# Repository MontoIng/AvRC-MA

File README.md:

# AvRC-MA
Avión RC - Monitoreo Ambiental
- En este proyecto se realizó un avión RC (Radio - Control) capaz de tomar datos de temperatura, presión y humedad.
(Santiago Montoya M.)
- Se subió cada codificación usada y creada en la realización del proyecto.
  Siendo asi estos: - Código del control.
                    - Código del Avión.
                    - Código para calibrar el motor.
                    - Librería BME280.
- Se organizó por carpeta los códigos, diseños (muestras - evidencias), documentos y PCBs.
- Se subieron los documentos respectivos a las carpetas.

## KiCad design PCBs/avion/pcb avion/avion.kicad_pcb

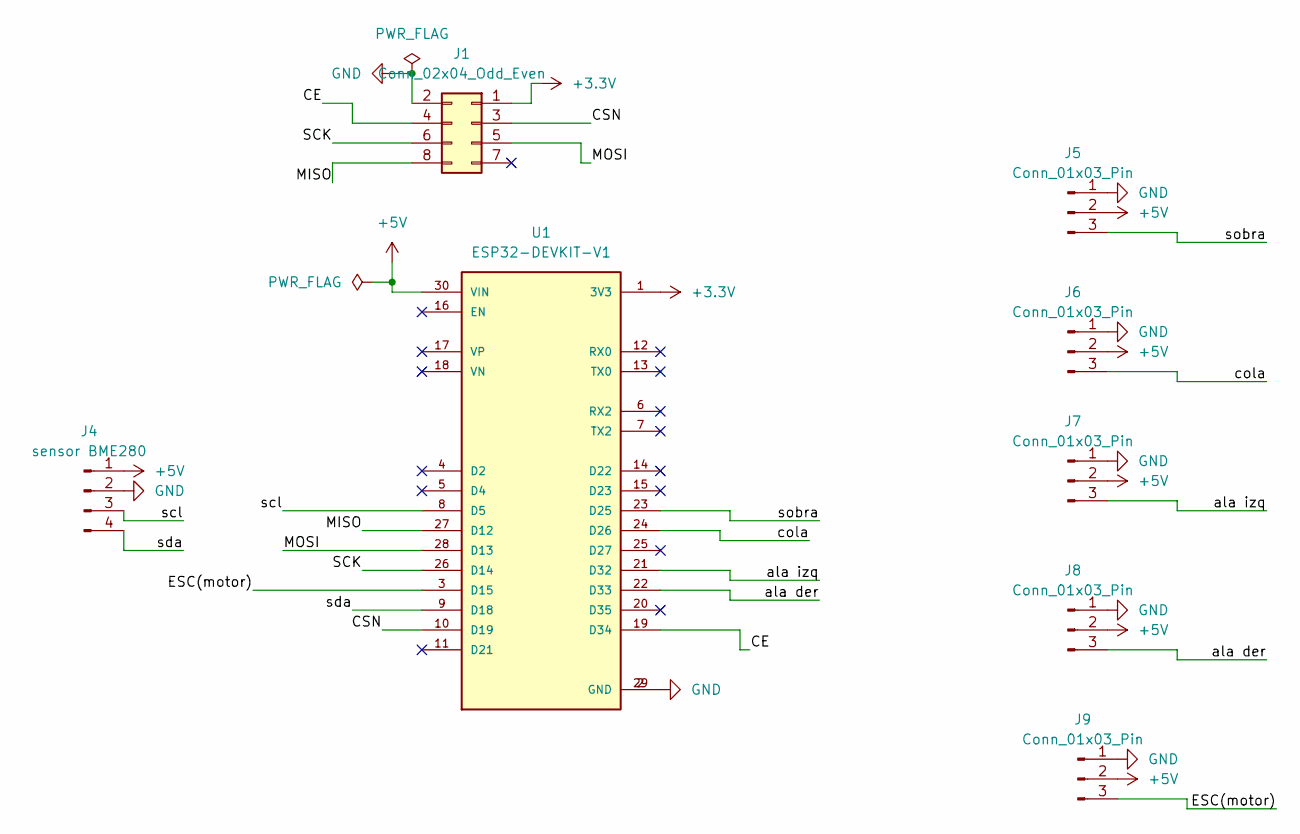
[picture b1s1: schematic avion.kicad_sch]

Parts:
J1: Conn_02x04_Odd_Even; PinSocket_2x04_P2.54mm_Vertical
J4: sensor BME280; PinHeader_1x04_P2.54mm_Vertical
J5, J6, J7, J8, J9: Conn_01x03_Pin; PinHeader_1x03_P2.54mm_Vertical
U1: ESP32-DEVKIT-V1; MODULE_ESP32_DEVKIT_V1; PARTREV N/A

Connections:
+3.3V: J1.1, U1.1 (3V3)
+5V: J4.1, J5.2, J6.2, J7.2, J8.2, J9.2, U1.30 (VIN)
/CE: J1.4, U1.19 (D34)
/CSN: J1.3, U1.10 (D19)
/ESC(motor): J9.3, U1.3 (D15)
/MISO: J1.8, U1.27 (D12)
/MOSI: J1.5, U1.28 (D13)
/SCK: J1.6, U1.26 (D14)
/ala der: J8.3, U1.22 (D33)
/ala izq: J7.3, U1.21 (D32)
/cola: J6.3, U1.24 (D26)
/scl: J4.3, U1.8 (D5)
/sda: J4.4, U1.9 (D18)
/sobra: J5.3, U1.23 (D25)
GND: J1.2, J4.2, J5.1, J6.1, J7.1, J8.1, J9.1, U1.2 (GND), U1.29 (GND)

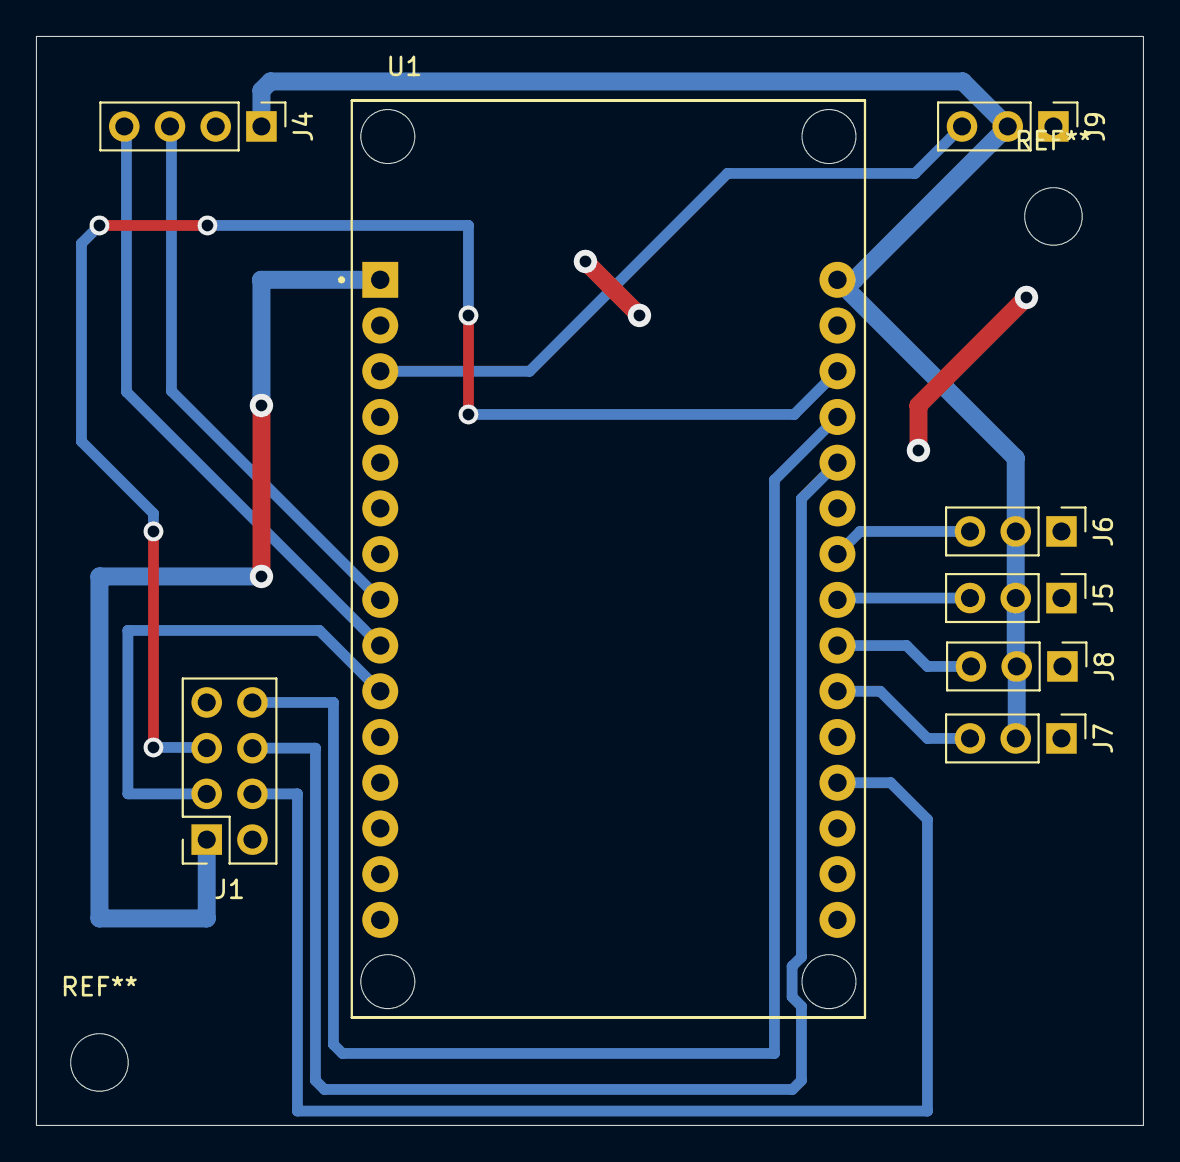
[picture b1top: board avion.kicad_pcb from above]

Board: 2 copper layers, 61.5 x 60.5 mm, 8 parts (0 on the bottom side), 15 nets.

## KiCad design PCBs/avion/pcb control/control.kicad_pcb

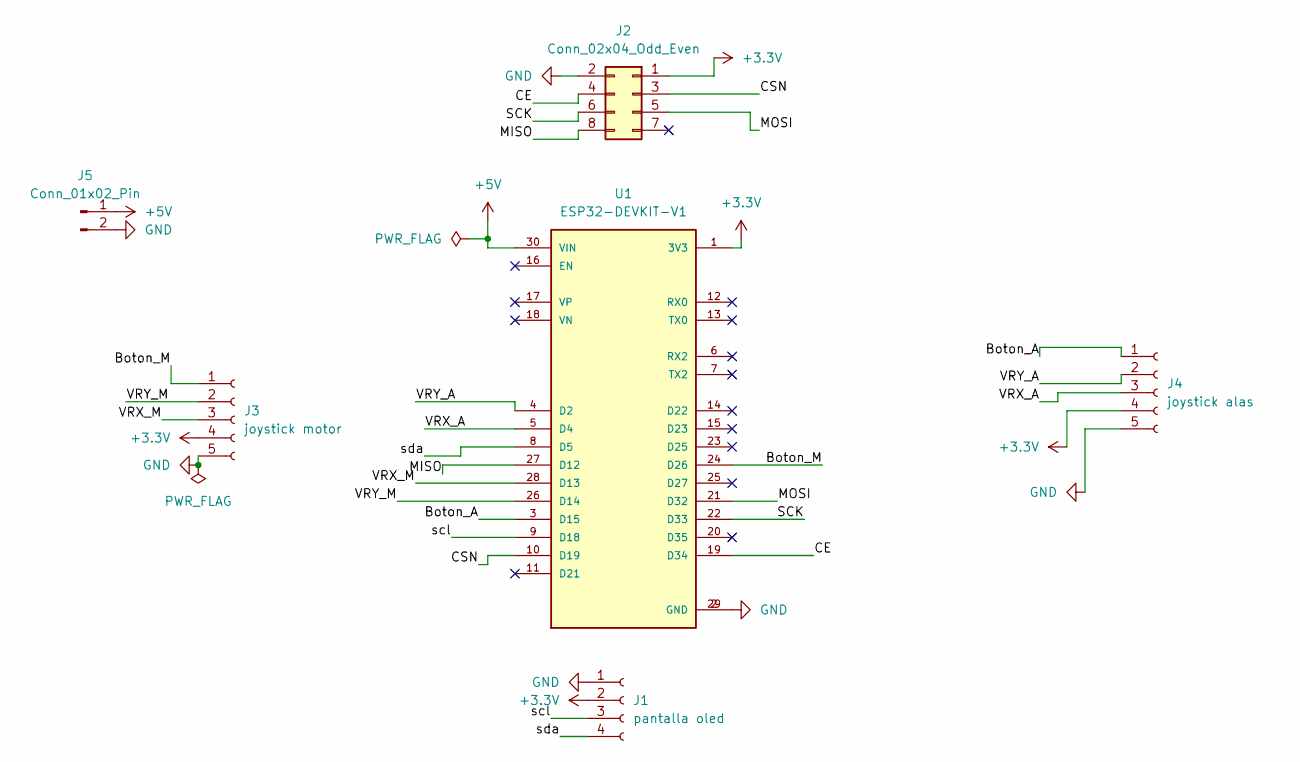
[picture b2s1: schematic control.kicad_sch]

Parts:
J1: pantalla oled; PinSocket_1x04_P2.54mm_Vertical
J2: Conn_02x04_Odd_Even; PinSocket_2x04_P2.54mm_Vertical
J3: joystick motor; PinSocket_1x05_P2.54mm_Horizontal
J4: joystick alas; PinSocket_1x05_P2.54mm_Horizontal
J5: Conn_01x02_Pin; PinHeader_1x02_P2.54mm_Vertical
U1: ESP32-DEVKIT-V1; MODULE_ESP32_DEVKIT_V1; PARTREV N/A

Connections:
+3.3V: J1.2, J2.1, J3.4, J4.4, U1.1 (3V3)
+5V: J5.1, U1.30 (VIN)
/Boton_A: J4.1, U1.3 (D15)
/Boton_M: J3.1, U1.24 (D26)
/CE: J2.4, U1.19 (D34)
/CSN: J2.3, U1.10 (D19)
/MISO: J2.8, U1.27 (D12)
/MOSI: J2.5, U1.21 (D32)
/SCK: J2.6, U1.22 (D33)
/VRX_A: J4.3, U1.5 (D4)
/VRX_M: J3.3, U1.28 (D13)
/VRY_A: J4.2, U1.4 (D2)
/VRY_M: J3.2, U1.26 (D14)
/scl: J1.3, U1.9 (D18)
/sda: J1.4, U1.8 (D5)
GND: J1.1, J2.2, J3.5, J4.5, J5.2, U1.2 (GND), U1.29 (GND)

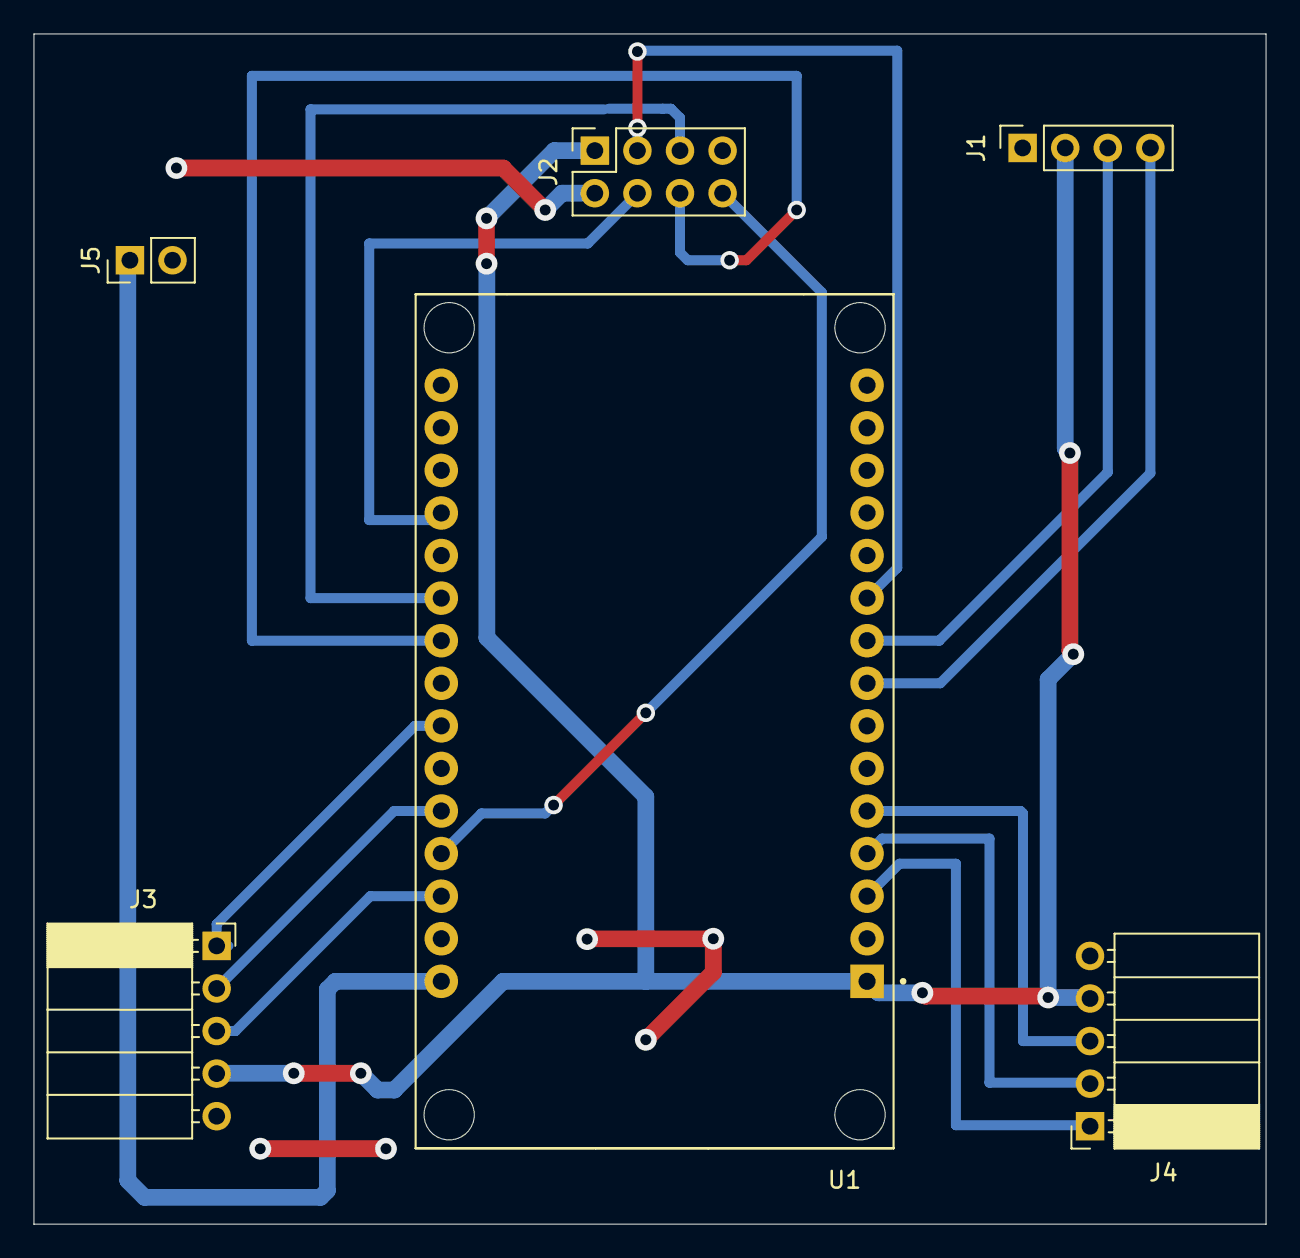
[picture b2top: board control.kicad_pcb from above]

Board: 2 copper layers, 73.5 x 71.0 mm, 6 parts (0 on the bottom side), 16 nets.

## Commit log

2024-09-18 Actualización README
    Se definió la función del proyecto
2024-09-18 Update README.md
    Primer integrante (cambio)
2024-09-25 Update Libs & Codification
    Se subieron y actualizaron tanto los códigos como las librerías.
2024-09-25 Update Files
    Se añaden en carpetas:
    - Documentos.
    - PCBs.
    - Diseños (muestras - evidencias).
2024-09-25 Update ReadMe
    Se dio descripción a las acciones realizadas.
2024-09-25 Update PCBs
    Se añade proyecto KiCad
2024-09-25 Update Documents
    Se suben imágenes restantes a la carpeta.
2024-09-25 Update Images
    Se actualizan imágenes/documentos completos de las PCBs y su creación en KiCad.
